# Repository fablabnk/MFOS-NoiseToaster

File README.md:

# MFOS Noise Toaster

> ##### Forked from *[Sam Zeter](https://github.com/samzeter/noise-toaster)*

## Status

Work in progress -> Revision 0.6.1

## Motivation

My first project to get back to electronics and learn something new along the way.
This repository is for the documentation of my journey to a fully functional analog synthesizer and may help other people to build one too.

This is my first electronics project for a long time and I decided to build the __Music From Outher Space -__ __*Noise Toaster*__,  because of the great documentation and the book 'Make: Analog Synthesizers' by Ray Wilson.

## How to use this repository

This repository contains all the files necessary for building the Noise Toaster, including the synth's PCB.  
If you intend to create your own PCB, simply compress all the files located in the 'PCB/Gerber Files' directory into a .zip file and upload it to the PCB manufacturer of your choice.   
In the directories 'classic design' and 'alternative design' (yet to come!) are all files to build the case of the Noise Toaster.    
For the front panels, I also created PCB designs, which you can upload to a manifacturer. Furthermore, there are CAD files and technical drawings (yet to come!) in the folders.   
The 'src' folder contains additional files which might be helpful.

## Project Structure
.  
│  
└── MFOS-NoiseToaster/  
&ensp;&ensp;&ensp;&ensp;│  
&ensp;&ensp;&ensp;&ensp;├── __'src/'__ &rarr; additional files and images that might be helpful for your own build   
&ensp;&ensp;&ensp;&ensp;├── __'classic design/'__ &rarr; all files to build the classic Noise Toaster case   
&ensp;&ensp;&ensp;&ensp;│&ensp;&ensp;&ensp;&ensp;├── __'CAD/'__  
&ensp;&ensp;&ensp;&ensp;│&ensp;&ensp;&ensp;&ensp;│&ensp;&ensp;&ensp;&ensp;└── '.FCstd' &rarr; FreeCAD files for the build    
&ensp;&ensp;&ensp;&ensp;│&ensp;&ensp;&ensp;&ensp;└── __'front panel/'__  
&ensp;&ensp;&ensp;&ensp;│&ensp;&ensp;&ensp;&ensp;&ensp;&ensp;&ensp;&ensp;&ensp;└── KiCAD files for front panel PCB &rarr; .zip this Geber files for the manufacturer   
&ensp;&ensp;&ensp;&ensp;├── __'PCB/'__   
&ensp;&ensp;&ensp;&ensp;│&ensp;&ensp;&ensp;&ensp;└── __'Gerber Files/'__ &rarr; .zip this directory for upload to the manufacturer  
&ensp;&ensp;&ensp;&ensp;│&ensp;&ensp;&ensp;&ensp;│&ensp;&ensp;&ensp;&ensp;└── *.gbr   
&ensp;&ensp;&ensp;&ensp;│&ensp;&ensp;&ensp;&ensp;└── 'Noise Toaster PCB.kicad_pcb'  
&ensp;&ensp;&ensp;&ensp;│&ensp;&ensp;&ensp;&ensp;└── ... &rarr; all files for the circuit diagram    
&ensp;&ensp;&ensp;&ensp;├── __'Bill of Material/'__   
&ensp;&ensp;&ensp;&ensp;│&ensp;&ensp;&ensp;&ensp;└── 'BoM checklist.md'  
&ensp;&ensp;&ensp;&ensp;│&ensp;&ensp;&ensp;&ensp;└── 'interactive BoM.html'    
&ensp;&ensp;&ensp;&ensp;├── README.md  
&ensp;&ensp;&ensp;&ensp;└── TODO.md  
&ensp;&ensp;&ensp;&ensp;└── licence.md &rarr; CC-BY-NC-SA  

## Usefull links and resources

* [Musik From Outer Space](http://musicfromouterspace.com/)
* [MFOS - Noise Toaster - Dokumentation](http://musicfromouterspace.com/index.php?MAINTAB=SYNTHDIY&PROJARG=NOISETOASTER/NOISETOASTER.php&VPW=1493&VPH=725)
* [Ray Wilson - YouTube Channel](https://www.youtube.com/@Musicfromouterspace)
* [MFOS Noise Toaster Presentation - Video by Ray Wilson](https://www.youtube.com/watch?v=smFKx6gfOd0)
* [Noise Toaster in action - Video by Ray Wilson](https://www.youtube.com/watch?v=qHlyuIe3wuU)
* [Make: Analog Synthesizers by Ray Wilson](https://learning.oreilly.com/library/view/make-analog-synthesizers/9781449356200/)

## For what's left TODO ...

[follow the White Rabbit!](TODO.md)

---

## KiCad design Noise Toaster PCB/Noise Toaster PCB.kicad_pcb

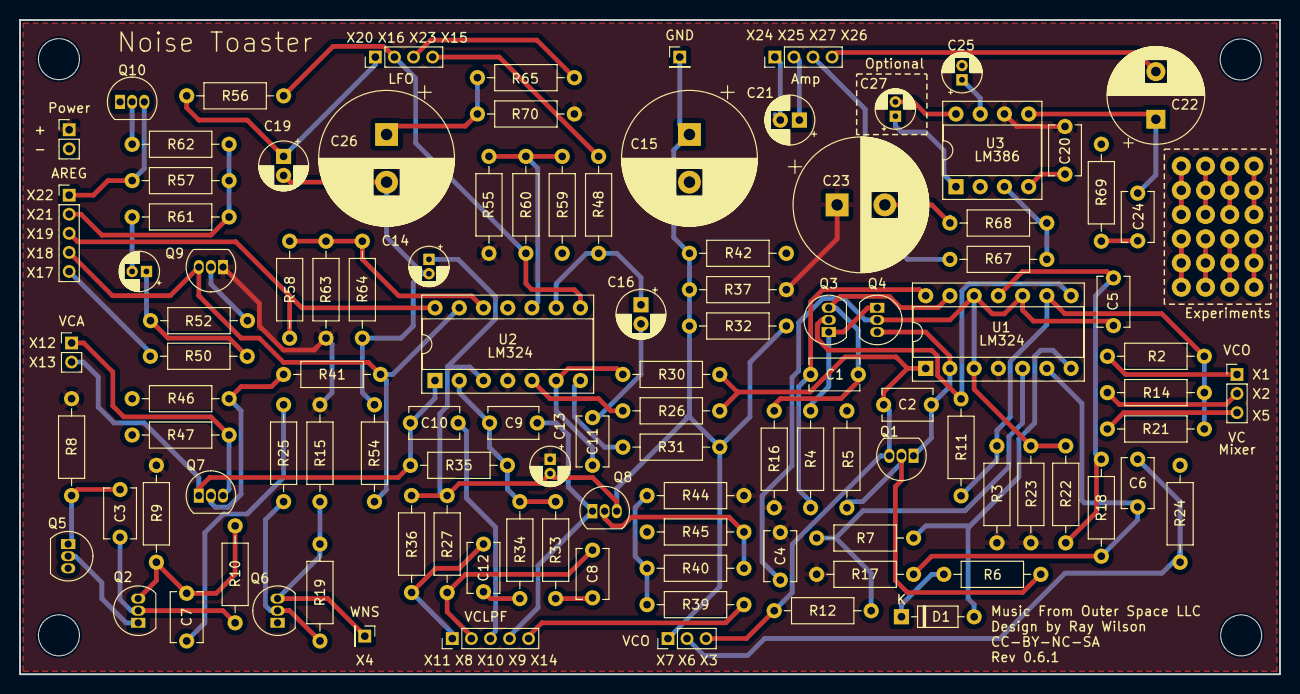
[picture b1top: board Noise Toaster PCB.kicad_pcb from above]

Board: 2 copper layers, 132.1 x 68.6 mm, 109 parts (0 on the bottom side), 68 nets.

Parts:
C1: 100 pF; C_Disc_D5.1mm_W3.2mm_P5.00mm
C2, C9, C10: 0.001 uF; C_Disc_D5.1mm_W3.2mm_P5.00mm
C3, C4, C5, C7, C8, C11, C12, C20: 0.1 uF; C_Disc_D5.1mm_W3.2mm_P5.00mm
C6: 0.01 uF; C_Disc_D5.1mm_W3.2mm_P5.00mm
C13, C14, C25, C27: 10 uF; CP_Radial_D4.0mm_P1.50mm
C15, C23, C26: 470 uF; CP_Radial_D14.0mm_P5.00mm
C16, C19, C21: 1 uF; CP_Radial_D5.0mm_P2.00mm
C18: 4.7 uF; CP_Radial_D4.0mm_P1.50mm
C22: 220 uF; CP_Radial_D10.0mm_P5.00mm
C24: 0.047 uF; C_Disc_D5.1mm_W3.2mm_P5.00mm
D1: D; D_DO-35_SOD27_P7.62mm_Horizontal
GND1: GND; PinHeader_1x01_P2.00mm_Vertical
J2: Power; PinHeader_1x02_P2.00mm_Vertical
J3: AREG; PinHeader_1x05_P2.00mm_Vertical
J4: LFO; PinHeader_1x04_P2.00mm_Vertical
J5, J6: VCO; PinHeader_1x03_P2.00mm_Vertical
J7: VCLPF; PinHeader_1x05_P2.00mm_Vertical
J8: VCA; PinHeader_1x02_P2.00mm_Vertical
J9: Amp; PinHeader_1x04_P2.00mm_Vertical
Q1, Q7, Q8, Q9: 2N5457; TO-92_Inline
Q2, Q3, Q4, Q5, Q6: 2N3904; TO-92_Inline
Q10: 2N3906; TO-92_Inline
R2: 75 K; R_Axial_DIN0207_L6.3mm_D2.5mm_P10.16mm_Horizontal
R3: 270 K; R_Axial_DIN0207_L6.3mm_D2.5mm_P10.16mm_Horizontal
R4, R6, R9, R12, R15, R17, R26, R32, R52, R61, R62: 10 K; R_Axial_DIN0207_L6.3mm_D2.5mm_P10.16mm_Horizontal
R5, R16, R30: 2 M; R_Axial_DIN0207_L6.3mm_D2.5mm_P10.16mm_Horizontal
R7: 300 K; R_Axial_DIN0207_L6.3mm_D2.5mm_P10.16mm_Horizontal
R8, R46: 1 M; R_Axial_DIN0207_L6.3mm_D2.5mm_P10.16mm_Horizontal
R10, R19, R41: 470 K; R_Axial_DIN0207_L6.3mm_D2.5mm_P10.16mm_Horizontal
R11: 2 K; R_Axial_DIN0207_L6.3mm_D2.5mm_P10.16mm_Horizontal
R14, R24, R25, R31, R44, R45, R47, R55, R58, R59, R60, R67: 100 K; R_Axial_DIN0207_L6.3mm_D2.5mm_P10.16mm_Horizontal
R18: 15 K; R_Axial_DIN0207_L6.3mm_D2.5mm_P10.16mm_Horizontal
R21: 36 K; R_Axial_DIN0207_L6.3mm_D2.5mm_P10.16mm_Horizontal
R22, R23: 4.7 K; R_Axial_DIN0207_L6.3mm_D2.5mm_P10.16mm_Horizontal
R27, R36: 47 K; R_Axial_DIN0207_L6.3mm_D2.5mm_P10.16mm_Horizontal
R33, R35: 4.7 M; R_Axial_DIN0207_L6.3mm_D2.5mm_P10.16mm_Horizontal
R34: 3 M; R_Axial_DIN0207_L6.3mm_D2.5mm_P10.16mm_Horizontal
R37, R42: 4.7 k; R_Axial_DIN0207_L6.3mm_D2.5mm_P10.16mm_Horizontal
R39, R40: 39 K; R_Axial_DIN0207_L6.3mm_D2.5mm_P10.16mm_Horizontal
R48, R65, R70: 3 K; R_Axial_DIN0207_L6.3mm_D2.5mm_P10.16mm_Horizontal
R50: 820 Ohm; R_Axial_DIN0207_L6.3mm_D2.5mm_P10.16mm_Horizontal
R54: 4,7 K; R_Axial_DIN0207_L6.3mm_D2.5mm_P10.16mm_Horizontal
R56, R68: 20 K; R_Axial_DIN0207_L6.3mm_D2.5mm_P10.16mm_Horizontal
R57: 200 Ohm; R_Axial_DIN0207_L6.3mm_D2.5mm_P10.16mm_Horizontal
R63, R64: 150 K; R_Axial_DIN0207_L6.3mm_D2.5mm_P10.16mm_Horizontal
R69: 10 Ohm; R_Axial_DIN0207_L6.3mm_D2.5mm_P10.16mm_Horizontal
U1, U2: LM324; DIP-14_W7.62mm_Socket
U3: LM386; DIP-8_W7.62mm_Socket
X4: WNS; PinHeader_1x01_P2.00mm_Vertical

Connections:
/AA: C2.1, Q1.1 (D), Q4.3 (C), U1.2 (-)
/ARG: J3.4, Q9.3 (S), R41.1, R54.2, U2.13 (-)
/Attack Release Envelope Generator/X17: J3.5, R50.2
/Attack Release Envelope Generator/X19: J3.3, R58.2, U2.14
/Attack Release Envelope Generator/X21: J3.2, R57.1, R61.2, R62.1
/Attack Release Envelope Generator/X22: J3.1, Q10.3 (C), R57.2
/Audio Amplifier/X24: C21.2, J9.1
/Audio Amplifier/X25: C21.1, J9.2
/Audio Amplifier/X26: C22.2, J9.4
/Audio Amplifier/X27: J9.3, R67.2
/FO: C10.2, J8.2, Q7.1 (D), R35.1, U2.1
/Front Panel/B: J4.2, R56.1, R60.2, U2.8
/Front Panel/X1: J5.1, R2.2
/Front Panel/X2: J5.2, R14.2
/Front Panel/X5: J5.3, R21.2
/Front Panel/X6: C6.1, J6.2, R24.1
/Front Panel/X8: C8.1, J7.2, R27.1
/Front Panel/X9: C9.1, J7.4, Q8.1 (D)
/Front Panel/X10: C10.1, J7.3
/Front Panel/X11: C12.1, J7.1, R36.2
/Front Panel/X12: J8.1, Q7.3 (S), R47.1
/Front Panel/X14: J7.5, R39.1
/Front Panel/X15: J4.4, R48.2
/Front Panel/X20: C19.1, J4.1, R56.2
/Front Panel/X23: J4.3, R65.2
/G2: C4.1, C5.1, Q4.2 (B), R22.1, R23.1, U1.3 (+), U1.10 (+), U1.12 (+)
/RMP: C2.2, J6.3, Q1.3 (S), R12.1, R26.1, R30.1, U1.1
/WNS: Q6.3 (C), R15.2, R19.1, X4.1
B+: C4.2, C13.1, C20.2, C23.1, J2.1, Q9.1 (D), R3.2, R8.1, R9.1, R15.1, R16.2, R17.2, R23.2, R37.1, R44.2, R55.1, R63.1, R70.2, U1.4 (V+), U2.4 (V+), U3.6 (V+)
B-: C5.2, C11.1, C14.2, C15.2, C16.2, C18.2, C19.2, C20.1, C23.2, C25.2, C26.2, J2.2, Q2.1 (E), Q5.2 (B), Q6.1 (E), Q10.1 (E), R5.2, R18.2, R22.2, R24.2, R42.2, R45.1, R46.2, R47.2, R54.1, R59.2, R61.1, R64.1, R68.2, R69.2, U1.11 (V-), U2.11 (V-), U3.2 (-), U3.4 (GND)
GND: C13.2, C14.1, C15.1, GND1.1, J6.1, Q8.3 (S), R27.2, R31.2, R32.1, R32.2, R36.1, R37.2, R42.1, U2.3 (+)
unnamed: C1.2, R4.2, U1.14
unnamed: C7.2, R25.1
unnamed: C8.2, R33.1
unnamed: C12.2, R34.1
unnamed: C18.1, R50.1, R52.1
unnamed: C22.1, C24.1, U3.5
unnamed: C24.2, R69.1
unnamed: C26.1, R65.1, R70.1
unnamed: C27.1, U3.1 (GAIN)
unnamed: C27.2, U3.8 (GAIN)
unnamed: D1.2 (A), R7.2, U1.7
unnamed: D1.1 (K), R6.2
unnamed: Q1.2 (G), R5.1, R6.1
unnamed: C3.2, Q2.2 (B), R10.2
unnamed: C7.1, Q2.3 (C), R9.2, R10.1
unnamed: Q3.2 (B), R11.2, U1.8
unnamed: C1.1, Q3.3 (C), R16.1, U1.13 (-)
unnamed: Q3.1 (E), Q4.1 (E), R4.1
unnamed: C3.1, Q5.1 (E), R8.2
unnamed: Q6.2 (B), R19.2, R25.2
unnamed: Q7.2 (G), R41.2, R46.1
unnamed: Q8.2 (G), R40.2, R45.2
unnamed: Q9.2 (G), R52.2
unnamed: Q10.2 (B), R62.2
unnamed: R31.1, U2.7
unnamed: R39.2, R40.1, R44.1
unnamed: R7.1, R12.2, U1.5 (+)
unnamed: C6.2, R17.1, R18.1, U1.6 (-)
unnamed: R2.1, R3.1, R11.1, R14.1, R21.1, U1.9 (-)
unnamed: C9.2, R33.2, R34.2, R35.2, U2.2 (-)
unnamed: R26.2, U2.5 (+)
unnamed: C11.2, R30.2, U2.6 (-)
unnamed: R55.2, R59.1, R60.1, U2.10 (+)
unnamed: C16.1, R48.1, U2.9 (-)
unnamed: R58.1, R63.2, R64.2, U2.12 (+)
unnamed: R67.1, R68.1, U3.3 (+)
unnamed: C25.1, U3.7 (BYPASS)

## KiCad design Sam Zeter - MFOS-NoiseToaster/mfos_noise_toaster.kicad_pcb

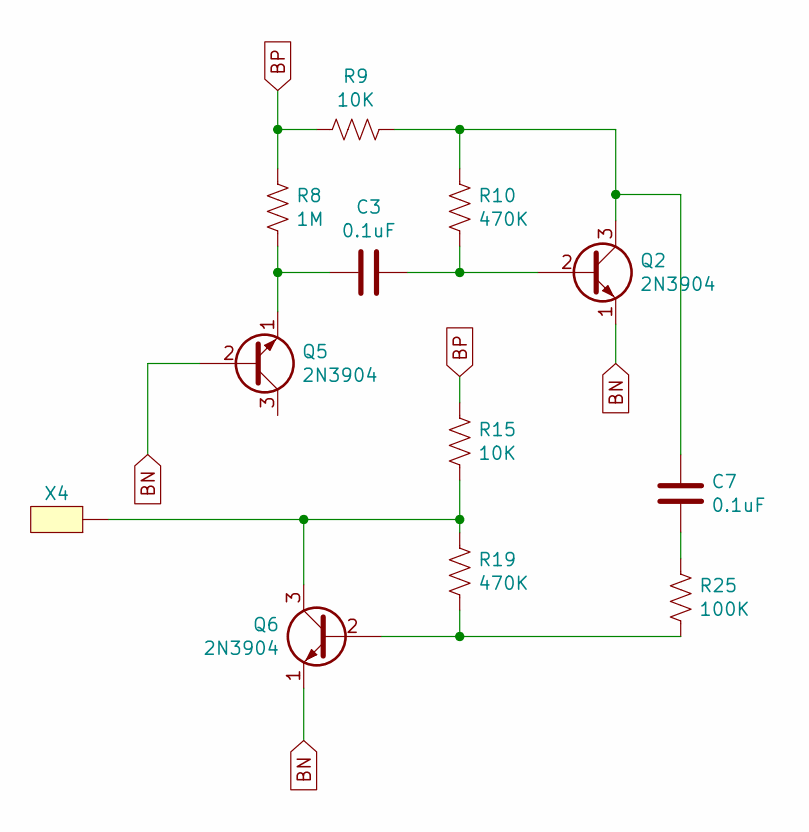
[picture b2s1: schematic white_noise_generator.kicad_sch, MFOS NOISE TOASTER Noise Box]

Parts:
C3, C7: 0.1uF; C_Disc_D5.0mm_W2.5mm_P3.50mm
Q2, Q5, Q6: 2N3904; TO-92_Inline
R8: 1M; R_Axial_DIN0207_L6.3mm_D2.5mm_P10.16mm_Horizontal
R9, R15: 10K; R_Axial_DIN0207_L6.3mm_D2.5mm_P10.16mm_Horizontal
R10, R19: 470K; R_Axial_DIN0207_L6.3mm_D2.5mm_P10.16mm_Horizontal
R25: 100K; R_Axial_DIN0207_L6.3mm_D2.5mm_P10.16mm_Horizontal
X4: Pad; pad

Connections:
BN: Q2.1 (E), Q5.2 (B), Q6.1 (E); also elsewhere on the board
BP: R8.1, R9.2, R15.1; also elsewhere on the board
unnamed: C3.1, Q2.2 (B), R10.2
unnamed: C3.2, Q5.1 (E), R8.2
unnamed: C7.1, R25.1
unnamed: C7.2, Q2.3 (C), R9.1, R10.1
unnamed: Q6.2 (B), R19.2, R25.2
unnamed: Q6.3 (C), R15.2, R19.1, X4.1

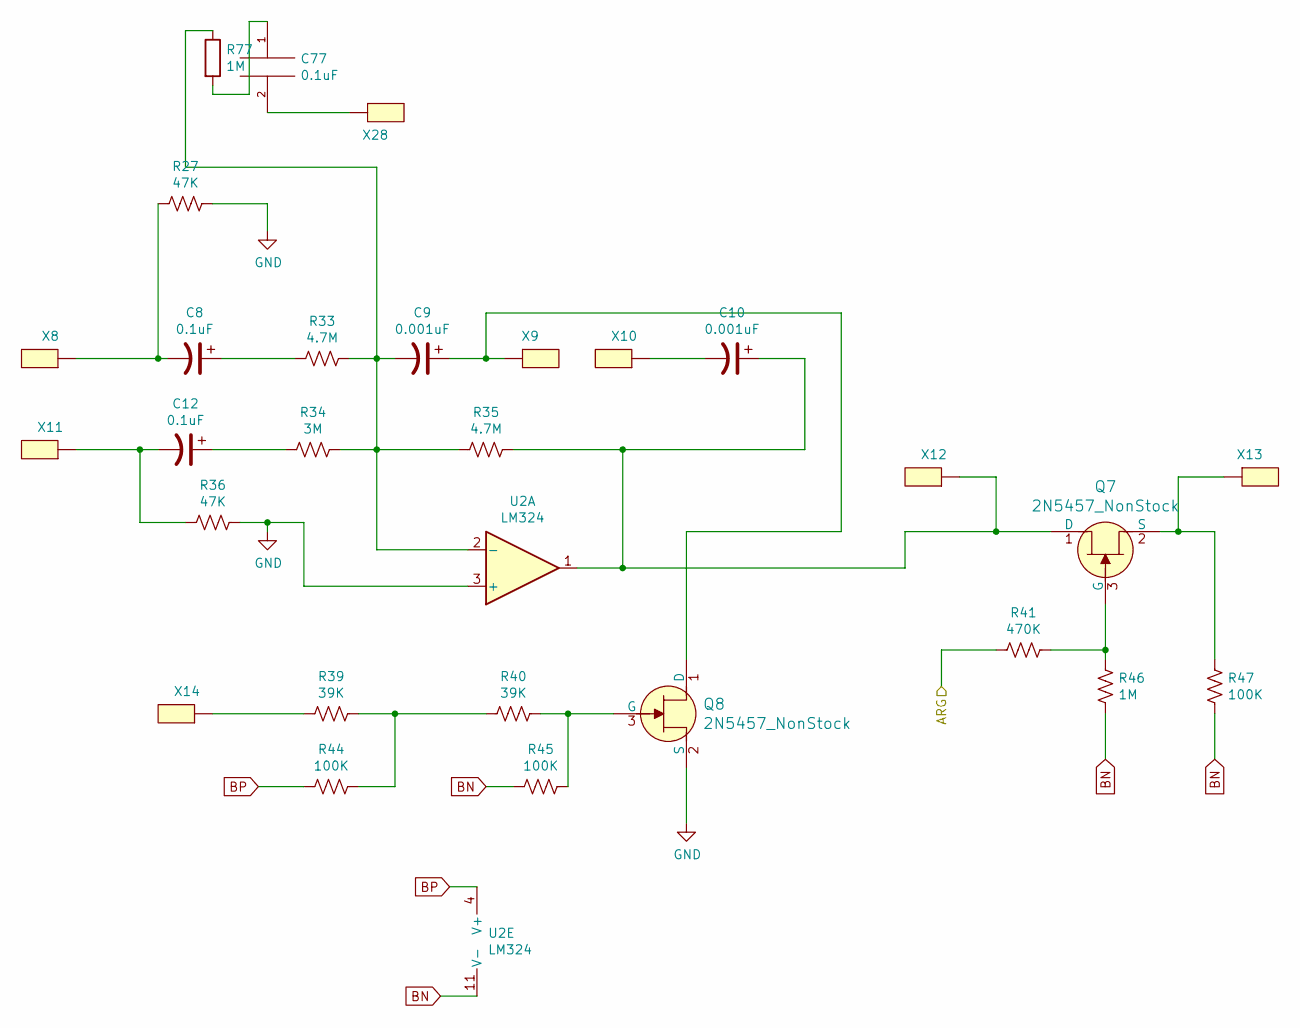
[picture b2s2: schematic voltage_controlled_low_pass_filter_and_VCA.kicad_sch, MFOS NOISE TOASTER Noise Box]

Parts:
C8, C12, C77: 0.1uF; C_Disc_D5.0mm_W2.5mm_P3.50mm
C9, C10: 0.001uF; C_Disc_D4.7mm_W2.5mm_P3.00mm
Q7, Q8: 2N5457_NonStock; TO-92-3; MPN 2N5457; Digi-Key_PN 2N5457-ND
R27, R36: 47K; R_Axial_DIN0207_L6.3mm_D2.5mm_P10.16mm_Horizontal
R33, R35: 4.7M; R_Axial_DIN0207_L6.3mm_D2.5mm_P10.16mm_Horizontal
R34: 3M; R_Axial_DIN0207_L6.3mm_D2.5mm_P10.16mm_Horizontal
R39, R40: 39K; R_Axial_DIN0207_L6.3mm_D2.5mm_P10.16mm_Horizontal
R41: 470K; R_Axial_DIN0207_L6.3mm_D2.5mm_P10.16mm_Horizontal
R44, R45, R47: 100K; R_Axial_DIN0207_L6.3mm_D2.5mm_P10.16mm_Horizontal
R46, R77: 1M; R_Axial_DIN0207_L6.3mm_D2.5mm_P10.16mm_Horizontal
U2: LM324; DIP-14_W7.62mm_LongPads
X8, X9, X10, X11, X12, X13, X14, X28: Pad; pad

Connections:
/attack_decay_generator/ARG: R41.1; also elsewhere on the board
BN: R45.2, R46.1, R47.1, U2.11 (V-); also elsewhere on the board
BP: R44.2, U2.4 (V+); also elsewhere on the board
GND: Q8.2 (S), R27.1, R36.1, U2.3 (+); also elsewhere on the board
unnamed: C8.1, R33.2
unnamed: C8.2, R27.2, X8.1
unnamed: C9.1, Q8.1 (D), X9.1
unnamed: C9.2, R33.1, R34.1, R35.2, R77.1, U2.2 (-)
unnamed: C10.1, Q7.1 (D), R35.1, U2.1, X12.1
unnamed: C10.2, X10.1
unnamed: C12.1, R34.2
unnamed: C12.2, R36.2, X11.1
unnamed: C77.1, R77.2
unnamed: C77.2, X28.1
unnamed: Q7.2 (S), R47.2, X13.1
unnamed: Q7.3 (G), R41.2, R46.2
unnamed: Q8.3 (G), R40.1, R45.1
unnamed: R39.1, R40.2, R44.1
unnamed: R39.2, X14.1

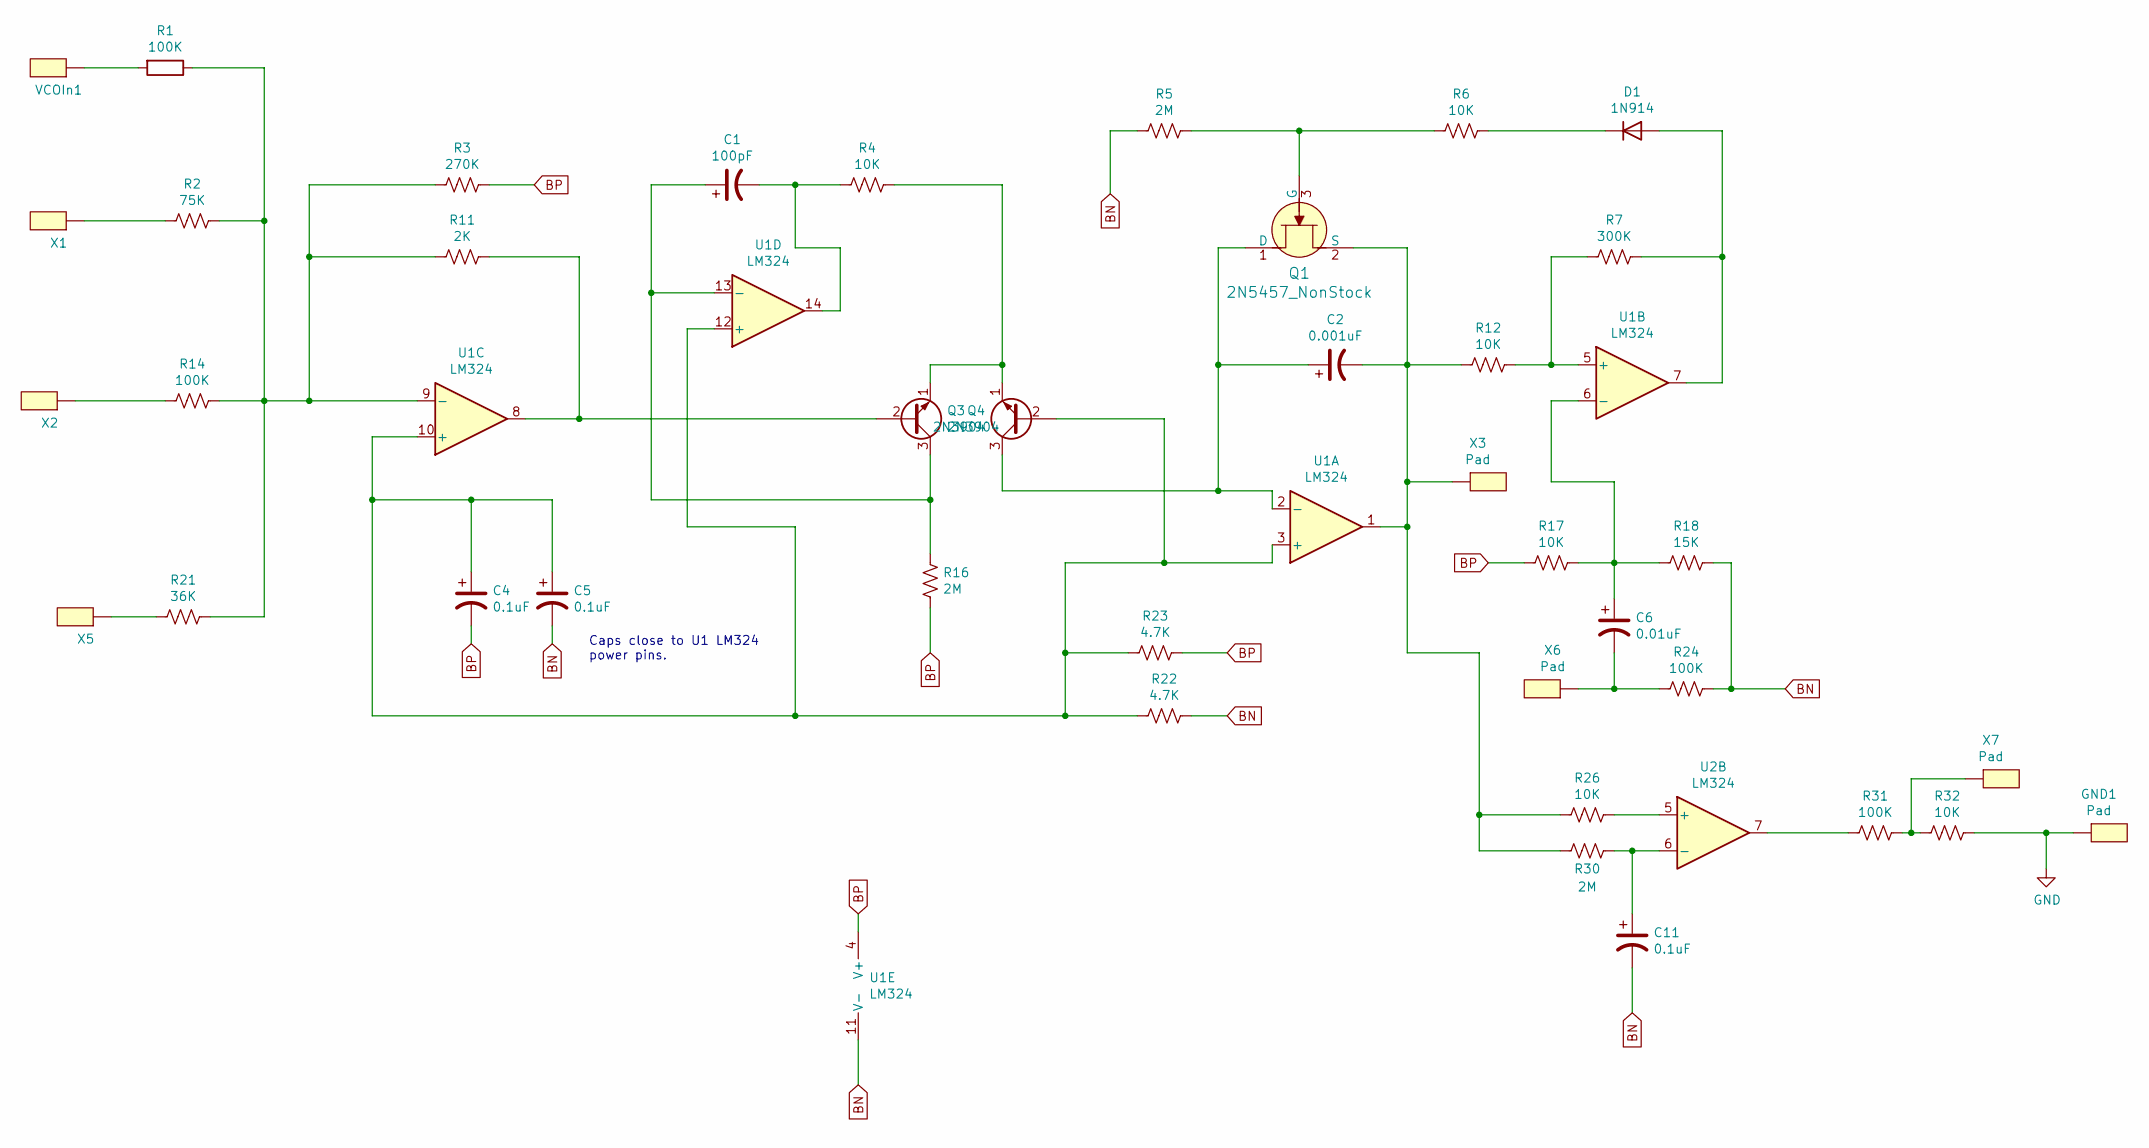
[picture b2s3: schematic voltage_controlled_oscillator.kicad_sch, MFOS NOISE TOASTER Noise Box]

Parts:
C1: 100pF; C_Disc_D3.4mm_W2.1mm_P2.50mm
C2: 0.001uF; C_Disc_D4.7mm_W2.5mm_P3.00mm
C4, C5, C11: 0.1uF; C_Disc_D5.0mm_W2.5mm_P3.50mm
C6: 0.01uF; C_Disc_D3.8mm_W2.6mm_P2.50mm
D1: 1N914; D_DO-35_SOD27_P7.62mm_Horizontal
GND1: Pad; pad
Q1: 2N5457_NonStock; TO-92-3; MPN 2N5457; Digi-Key_PN 2N5457-ND
Q3, Q4: 2N3904; TO-92_Inline
R1, R14, R24, R31: 100K; R_Axial_DIN0207_L6.3mm_D2.5mm_P10.16mm_Horizontal
R2: 75K; R_Axial_DIN0207_L6.3mm_D2.5mm_P10.16mm_Horizontal
R3: 270K; R_Axial_DIN0207_L6.3mm_D2.5mm_P10.16mm_Horizontal
R4, R6, R12, R17, R26, R32: 10K; R_Axial_DIN0207_L6.3mm_D2.5mm_P10.16mm_Horizontal
R5, R16, R30: 2M; R_Axial_DIN0207_L6.3mm_D2.5mm_P10.16mm_Horizontal
R7: 300K; R_Axial_DIN0207_L6.3mm_D2.5mm_P10.16mm_Horizontal
R11: 2K; R_Axial_DIN0207_L6.3mm_D2.5mm_P10.16mm_Horizontal
R18: 15K; R_Axial_DIN0207_L6.3mm_D2.5mm_P10.16mm_Horizontal
R21: 36K; R_Axial_DIN0207_L6.3mm_D2.5mm_P10.16mm_Horizontal
R22, R23: 4.7K; R_Axial_DIN0207_L6.3mm_D2.5mm_P10.16mm_Horizontal
U1, U2: LM324; DIP-14_W7.62mm_LongPads
VCOIn1: Pad; pad
X1, X2, X3, X5, X6, X7: Pad; pad

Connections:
BN: C5.2, C11.2, R5.2, R18.1, R22.1, R24.1, U1.11 (V-); also elsewhere on the board
BP: C4.2, R3.1, R16.2, R17.2, R23.1, U1.4 (V+); also elsewhere on the board
GND: GND1.1, R32.1; also elsewhere on the board
unnamed: C1.1, Q3.3 (C), R16.1, U1.13 (-)
unnamed: C1.2, R4.2, U1.14
unnamed: C2.1, Q1.1 (D), Q4.3 (C), U1.2 (-)
unnamed: C2.2, Q1.2 (S), R12.2, R26.2, R30.2, U1.1, X3.1
unnamed: C4.1, C5.1, Q4.2 (B), R22.2, R23.2, U1.3 (+), U1.10 (+), U1.12 (+)
unnamed: C6.1, R17.1, R18.2, U1.6 (-)
unnamed: C6.2, R24.2, X6.1
unnamed: C11.1, R30.1, U2.6 (-)
unnamed: D1.1 (K), R6.1
unnamed: D1.2 (A), R7.1, U1.7
unnamed: Q1.3 (G), R5.1, R6.2
unnamed: Q3.1 (E), Q4.1 (E), R4.1
unnamed: Q3.2 (B), R11.1, U1.8
unnamed: R1.1, R2.1, R3.2, R11.2, R14.1, R21.1, U1.9 (-)
unnamed: R1.2, VCOIn1.1
unnamed: R2.2, X1.1
unnamed: R7.2, R12.1, U1.5 (+)
unnamed: R14.2, X2.1
unnamed: R21.2, X5.1
unnamed: R26.1, U2.5 (+)
unnamed: R31.1, R32.2, X7.1
unnamed: R31.2, U2.7

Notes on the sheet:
Caps close to U1 LM324 power pins.

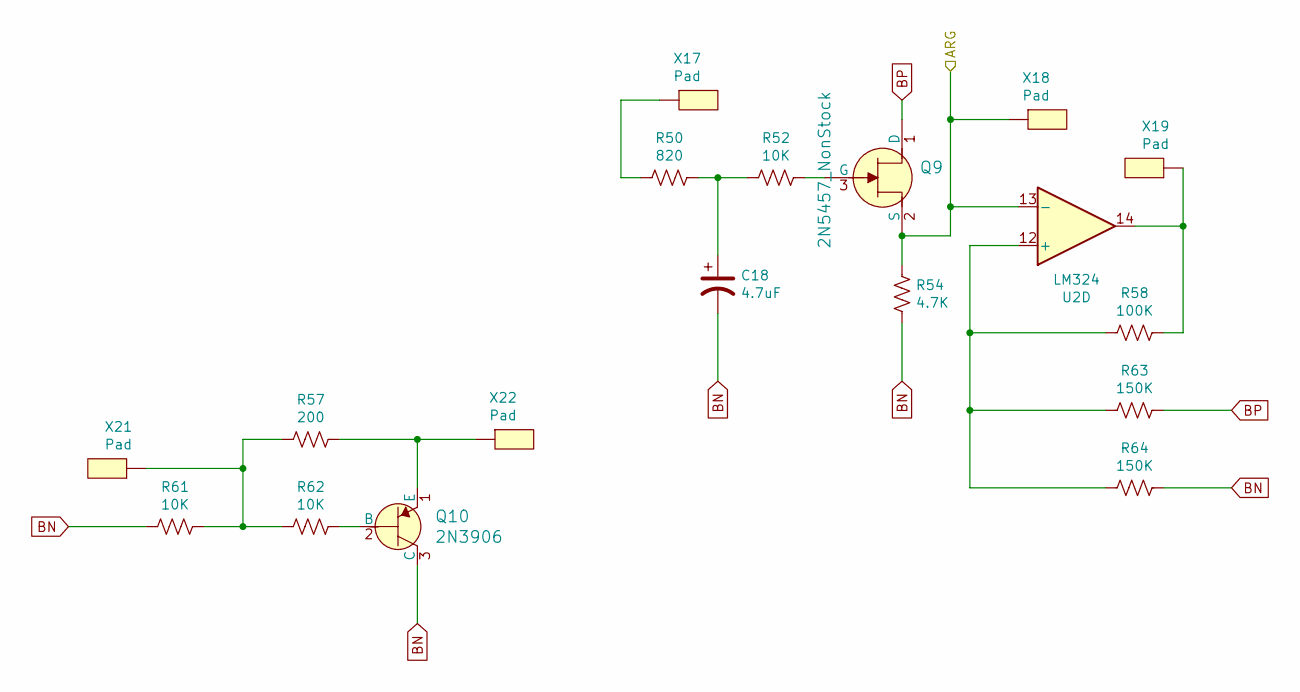
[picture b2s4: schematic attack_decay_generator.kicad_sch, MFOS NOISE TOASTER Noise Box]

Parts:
C18: 4.7uF; CP_Radial_D5.0mm_P2.50mm
Q9: 2N5457_NonStock; TO-92-3; MPN 2N5457; Digi-Key_PN 2N5457-ND
Q10: 2N3906; TO-92-3; MPN 2N3906; Digi-Key_PN 2N3906CS-ND
R50: 820; R_Axial_DIN0207_L6.3mm_D2.5mm_P10.16mm_Horizontal
R52, R61, R62: 10K; R_Axial_DIN0207_L6.3mm_D2.5mm_P10.16mm_Horizontal
R54: 4.7K; R_Axial_DIN0207_L6.3mm_D2.5mm_P10.16mm_Horizontal
R57: 200; R_Axial_DIN0207_L6.3mm_D2.5mm_P10.16mm_Horizontal
R58: 100K; R_Axial_DIN0207_L6.3mm_D2.5mm_P10.16mm_Horizontal
R63, R64: 150K; R_Axial_DIN0207_L6.3mm_D2.5mm_P10.16mm_Horizontal
U2: LM324; DIP-14_W7.62mm_LongPads
X17, X18, X19, X21, X22: Pad; pad

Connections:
/attack_decay_generator/ARG: Q9.2 (S), R54.2, U2.13 (-), X18.1; also elsewhere on the board
BN: C18.2, Q10.3 (C), R54.1, R61.2, R64.1; also elsewhere on the board
BP: Q9.1 (D), R63.1; also elsewhere on the board
unnamed: C18.1, R50.1, R52.2
unnamed: Q9.3 (G), R52.1
unnamed: Q10.1 (E), R57.1, X22.1
unnamed: Q10.2 (B), R62.1
unnamed: R50.2, X17.1
unnamed: R57.2, R61.1, R62.2, X21.1
unnamed: R58.1, U2.14, X19.1
unnamed: R58.2, R63.2, R64.2, U2.12 (+)

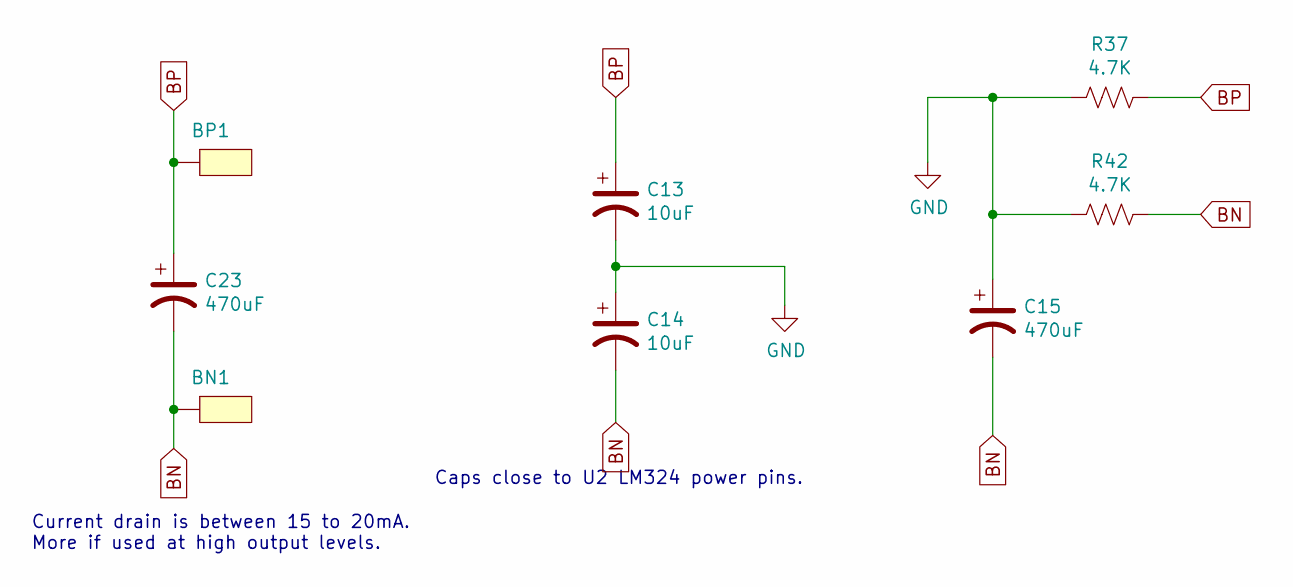
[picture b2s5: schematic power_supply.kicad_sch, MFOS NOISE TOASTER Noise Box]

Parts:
BN1: Pad-samz-symbol; pad
BP1: Pad-samz-symbol; pad
C13, C14: 10uF; CP_Radial_D5.0mm_P2.50mm
C15, C23: 470uF; CP_Radial_D10.0mm_P5.50mm
R37, R42: 4.7K; R_Axial_DIN0207_L6.3mm_D2.5mm_P10.16mm_Horizontal

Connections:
BN: BN1.1, C14.2, C15.2, C23.2, R42.1; also elsewhere on the board
BP: BP1.1, C13.1, C23.1, R37.1; also elsewhere on the board
GND: C13.2, C14.1, C15.1, R37.2, R42.2; also elsewhere on the board

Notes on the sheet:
Caps close to U2 LM324 power pins.
Current drain is between 15 to 20mA. More if used at high output levels.

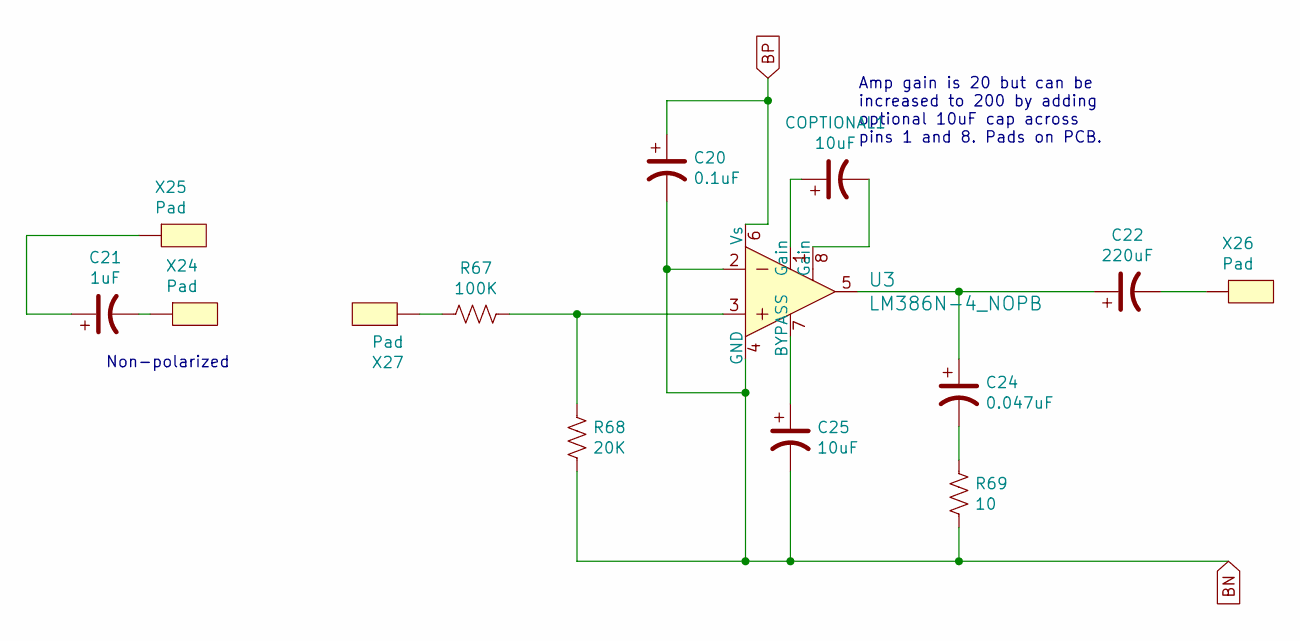
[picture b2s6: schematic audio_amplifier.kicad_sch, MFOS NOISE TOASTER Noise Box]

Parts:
C20: 0.1uF; C_Disc_D5.0mm_W2.5mm_P3.50mm
C21: 1uF; CP_Radial_D5.0mm_P2.50mm
C22: 220uF; CP_Radial_D10.0mm_P5.00mm
C24: 0.047uF; C_Disc_D3.4mm_W2.1mm_P2.50mm
C25: 10uF; CP_Radial_D5.0mm_P2.50mm
COPTIONAL1: 10uF; CP_Radial_D5.0mm_P2.50mm
R67: 100K; R_Axial_DIN0207_L6.3mm_D2.5mm_P10.16mm_Horizontal
R68: 20K; R_Axial_DIN0207_L6.3mm_D2.5mm_P10.16mm_Horizontal
R69: 10; R_Axial_DIN0207_L6.3mm_D2.5mm_P10.16mm_Horizontal
U3: LM386N-4_NOPB; DIP-8_W7.62mm; MPN LM386N-4/NOPB; Digi-Key_PN 296-43960-5-ND
X24, X25, X26, X27: Pad; pad

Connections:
BN: C20.2, C25.2, R68.2, R69.2, U3.2, U3.4 (GND); also elsewhere on the board
BP: C20.1, U3.6 (Vs); also elsewhere on the board
unnamed: C21.1, X25.1
unnamed: C21.2, X24.1
unnamed: C22.1, C24.1, U3.5
unnamed: C22.2, X26.1
unnamed: C24.2, R69.1
unnamed: C25.1, U3.7 (BYPASS)
unnamed 36: COPTIONAL1.1, U3.1 (Gain); also elsewhere on the board
unnamed 37: COPTIONAL1.2, U3.8 (Gain); also elsewhere on the board
unnamed: R67.1, R68.1, U3.3
unnamed: R67.2, X27.1

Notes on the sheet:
Non-polarized
Amp gain is 20 but can be increased to 200 by adding optional 10uF cap across pins 1 and 8. Pads on PCB.

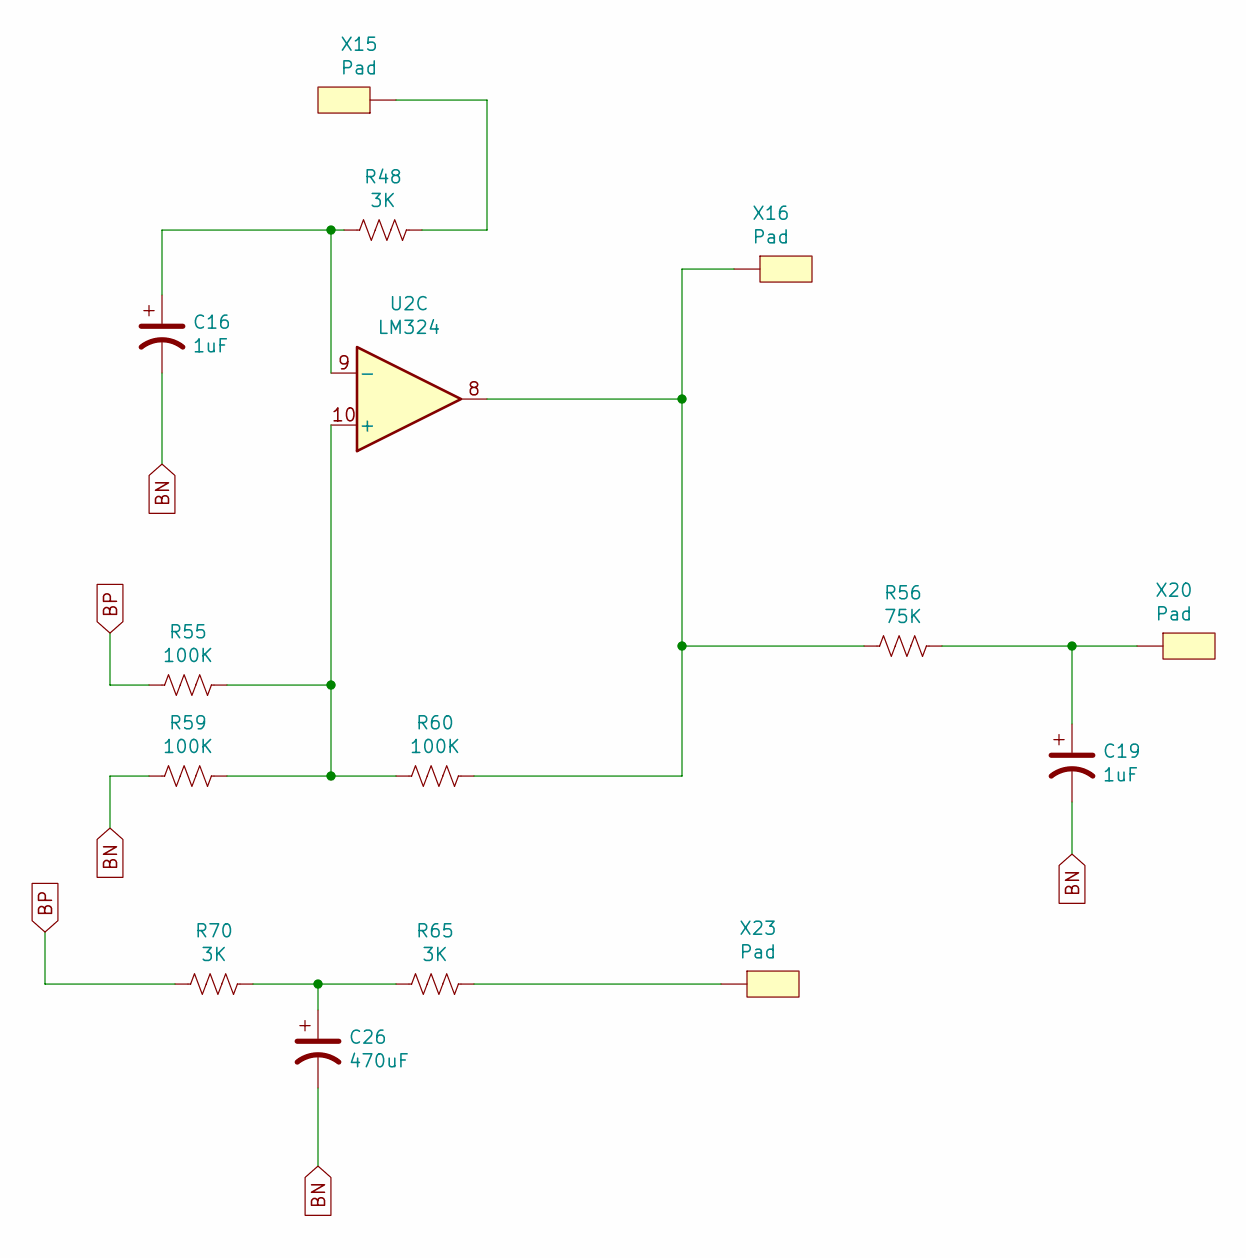
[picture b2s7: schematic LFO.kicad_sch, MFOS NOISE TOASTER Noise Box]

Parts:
C16, C19: 1uF; CP_Radial_D5.0mm_P2.50mm
C26: 470uF; CP_Radial_D10.0mm_P5.00mm
R48, R65, R70: 3K; R_Axial_DIN0207_L6.3mm_D2.5mm_P10.16mm_Horizontal
R55, R59, R60: 100K; R_Axial_DIN0207_L6.3mm_D2.5mm_P10.16mm_Horizontal
R56: 75K; R_Axial_DIN0207_L6.3mm_D2.5mm_P10.16mm_Horizontal
U2: LM324; DIP-14_W7.62mm_LongPads
X15, X16, X20, X23: Pad; pad

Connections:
BN: C16.2, C19.2, C26.2, R59.2; also elsewhere on the board
BP: R55.2, R70.2; also elsewhere on the board
unnamed: C16.1, R48.2, U2.9 (-)
unnamed: C19.1, R56.1, X20.1
unnamed: C26.1, R65.2, R70.1
unnamed: R48.1, X15.1
unnamed: R55.1, R59.1, R60.2, U2.10 (+)
unnamed: R56.2, R60.1, U2.8, X16.1
unnamed: R65.1, X23.1

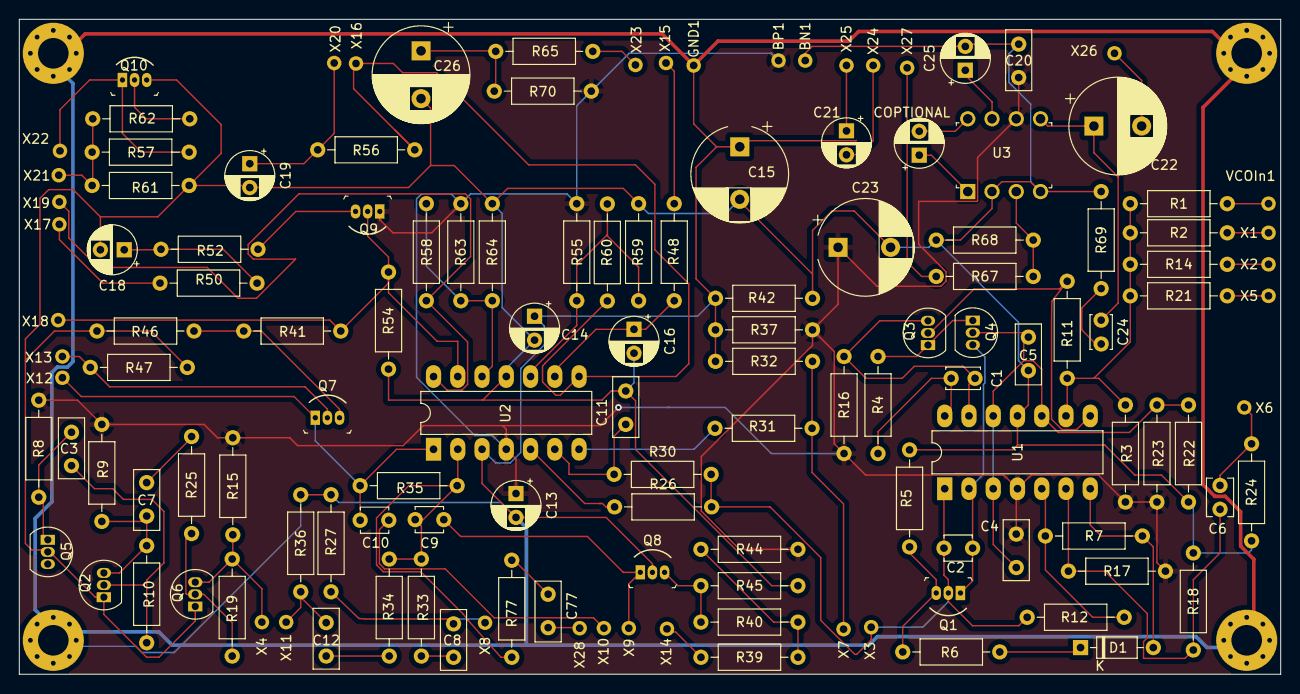
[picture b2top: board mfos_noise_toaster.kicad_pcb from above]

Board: 2 copper layers, 132.1 x 68.6 mm, 134 parts (0 on the bottom side), 72 nets.

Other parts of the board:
COPTIONAL: 10uF; CP_Radial_D5.0mm_P2.50mm

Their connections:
unnamed 36: COPTIONAL.1; also elsewhere on the board
unnamed 37: COPTIONAL.2; also elsewhere on the board

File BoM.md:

# Bill of Materials for MFOS Noise Toaster


### Active Components
|   Check  |    Qty   | Description | Value/Note | Designators |
|:--------:|:--------:|:-----------:|:----------:|:-----------:|
| &#9744;  | 2 | LM324 Quad Low Power Op Amp | 14 pin DIP | U1, U2 |
| &#9744;  | 1 | LM386N4 (or N3) Low Voltage Audio Power Amp | 8 pin DIP | U3 |
| &#9744;  | 1 | 2N3906 PNP Transistor | T092 | Q10 |
| &#9744;  | 4 | 2N5457 N Channel JFET | T092 | Q1, Q7, Q8, Q9 |
| &#9744;  | 5 | 2N3904 NPN Transistor | T092 | Q2, Q3, Q4, Q5, Q6 |
| &#9744;  | 3 | 1N914 High Speed Sw. Diode | D0-35 | D1, D2, D3 |
| &#9744;  | 1 | LED | General Purpose | LED1 |
| &#9744;  | 2 | 14 pin DIP IC Socket | High Reliability |  |
| &#9744;  | 1 | 8 pin DIP IC Socket | High Reliability |  |

### Resistors and Pots
|   Check  |    Qty   | Description | Value/Note | Designators |
|:--------:|:--------:|:-----------:|:----------:|:-----------:|
| &#9744;  | 7 | Linear Taper Potentiometer | 100 k&ohm; | R1, R13, R20, R28, R29, R38, R66 |
| &#9744;  | 3 | Linear Taper Potentiometer | 1 M&ohm; | R49, R51, R53 |
| &#9744;  | 3 | Resistor 0,25 W 5 % | 2 M&ohm; | R5, R16, R53 |
| &#9744;  | 1 | Resistor 0,25 W 5 % | 300 k&ohm; | R7 |
| &#9744;  | 1 | Resistor 0,25 W 5 % | 36 k&ohm; | R21 |
| &#9744;  | 1 | Resistor 0,25 W 5 % | 15 k&ohm; | R18 |
| &#9744;  | 2 | Resistor 0,25 W 5 % | 39 k&ohm; | R39, R40 |
| &#9744;  | 3 | Resistor 0,25 W 5 % | 3 k&ohm; | R48, R65, R70 |
| &#9744;  | 5 | Resistor 0,25 W 5 % | 4.7 k&ohm; | R22, R23, R37, R42, R54 |
| &#9744;  | 2 | Resistor 0,25 W 5 % | 4.7 M&ohm; | R33, R35 |
| &#9744;  | 3 | Resistor 0,25 W 5 % | 470 k&ohm; | R10, R19, R41 |
| &#9744;  | 2 | Resistor 0,25 W 5 % | 47 k&ohm; | R27, R36 |
| &#9744;  | 1 | Resistor 0,25 W 5 % | 75 k&ohm; | R2 |
| &#9744;  | 1 | Resistor 0,25 W 5 % | 820 &ohm; | R50 |
| &#9744;  | 1 | Resistor 0,25 W 5 % | 10 &ohm; | R69 |
| &#9744;  | 12 | Resistor 0,25 W 5 % | 100 k&ohm; | R14, R24, R25, R31, R44, R45, R47, R55, R58, R59, R60, R67 |
| &#9744;  | 11 | Resistor 0,25 W 5 % | 10 k&ohm; | R4, R6, R9, R12, R15, R17, R26, R32, R52, R61, R62  |
| &#9744;  | 2 | Resistor 0,25 W 5 % | 150 &ohm; | R63, R64 |
| &#9744;  | 1 | Resistor 0,25 W 5 % | 3 M&ohm; | R34 |
| &#9744;  | 2 | Resistor 0,25 W 5 % | 1 M&ohm; | R8, R46 |
| &#9744;  | 1 | Resistor 0,25 W 5 % | 200 &ohm; | R57 |
| &#9744;  | 2 | Resistor 0,25 W 5 % | 20 k&ohm; | R68, R56 |
| &#9744;  | 1 | Resistor 0,25 W 5 % | 270 k&ohm; | R3 |
| &#9744;  | 1 | Resistor 0,25 W 5 % | 27 k&ohm; | R43 |
| &#9744;  | 1 | Resistor 0,25 W 5 % | 2 k&ohm; | R11 |

### Capacitors
|   Check  |    Qty   | Description | Value/Note | Designators |
|:--------:|:--------:|:-----------:|:----------:|:-----------:|
| &#9744;  | 2 | Capacitor Aluminum Bipolar (nonpolarized) | 1 &micro;F | C17, C21 |
| &#9744;  | 3 | Capacitor Ceramic | 0.001 &micro;F / 1 nF | C2, C9, C10 |
| &#9744;  | 1 | Capacitor Ceramic | 0.047 &micro;F / 47 nF | C24 |
| &#9744;  | 8 | Capacitor Ceramic | 0.1 &micro;F / 100 nF | C3, C4, C5, C7, C8, C11, C12, C20 |
| &#9744;  | 1 | Capacitor Ceramic | 100 pF | C1 |
| &#9744;  | 1 | Capacitor Ceramic | 0.01 &micro;F / 10 nF | C6 |
| &#9744;  | 3 | Capacitor Electrolytic | 10 &micro;F | C13, C14, C25 |
| &#9744;  | 2 | Capacitor Electrolytic | 1 &micro;F | C16, C19 |
| &#9744;  | 1 | Capacitor Electrolytic | 4.7 &micro;F | C18 |
| &#9744;  | 1 | Capacitor Electrolytic Radial Lead 0.2" Spacing | 220 &micro;F | C22 |
| &#9744;  | 3 | Capacitor Electrolytic Radial Lead 0.2" Spacing | 470 &micro;F | C15, C23, C26 |

### Hardware and Other Components
|   Check  |    Qty   | Description | Value/Note | Designators |
|:--------:|:--------:|:-----------:|:----------:|:-----------:|
| &#9744;  | 1 | Speaker 2 1/4" | 8 &ohm; 1 W | SPK1 |
| &#9744;  | 2 | Switch SPDT (Center Off) Mini Toggle | SPDT C.O. | S3, S6 |
| &#9744;  | 2 | Switch SPDT Mini Toggle | SPDT | S8, S9 |
| &#9744;  | 6 | Switch SPST Mini Toggle | SPST | S1, S2, S4, S5, S7, S11 |
| &#9744;  | 1 | Switch SPST N.O. Pushbutton | SPST | S10 |
| &#9744;  | 1 | Jack 1/4" with NC Switch to Tip |  | J1 |
| &#9744;  | 1 | 9V Alkaline Battery |  | B1 |
| &#9744;  | 1 | 9V Battery Snap Connector |  |  |
| &#9744;  | 1 | 9V Battery Holder |  |  |
| &#9744;  | 1 | Projec Case 7 * 7 * 2" |  |  |
| &#9744;  | 2 | 6-32 1 1/4" Screws |  |  |
| &#9744;  | 4 | 6-32 Screw Nuts |  |  |
| &#9744;  | 4 | 1/4" W x 3/8" L Nylon Spacers |  | 1 |

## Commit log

2023-07-12 added own README as test
2023-07-12 added README.md
2023-07-12 added .gitignore
2023-07-12 refactored the gerber files
2023-07-12 fixed typo because me at english bad o_O
2023-07-17 added Bills of Materials as .md file
2023-07-17 fixed check box
2023-07-30 added the classic noise toaster front panel design
2023-07-30 updated rotary scales of the front panel design
2023-07-30 added invertet front panel version
2023-08-07 updated .gitignore with KiCad files
2023-08-07 added a proper license for the files
2023-08-07 fixed typo
2023-08-21 updated TODO
2023-08-21 updated .gitignore file
2023-08-21 commiting my KiCad schematics
2023-08-21 updated .gitignore
2023-08-21 outsourced TODO and added project structure
2023-08-21 updated project structure and front panel dir
2023-08-21 added seperated TODO.md file
2023-08-21 updated tree view
2023-08-21 fixed tree view
2023-08-23 beatified the tree view
2023-08-24 updated schematics
2023-08-26 erstelle test.txt
2023-08-26 cloned sam zeters original repository
2023-08-26 deleted unnecessary files
2023-08-26 try to resole '2 commits behind messsage'
2023-08-26 solved issues
2023-08-26 fixed final gerber location
2023-08-26 refactored the schematic
2023-09-10 refactored schematics and added front panel
2023-09-10 beautified README and fixed typo
2023-09-10 added lost .gitignore
2023-09-10 cleared gitignore cache
2023-09-10 fixed typo in gitignore
2023-09-10 fixed another typo
2023-09-10 removed old pcb files
2023-09-10 color coded wireing and added color legend
2023-09-10 front panel components excluded from circuit board
2023-09-10 fixed legend
2023-09-10 wireing and components have been checked
2023-09-12 applied footprints
2023-09-17 placed pards of the pcb properly
2023-09-18 created pcb file
2023-09-18 created gerber files
2023-09-18 created interactive BoM
2023-09-18 added .zip files to .gitignore
2023-09-18 updated project structure section
2023-09-18 updated tree few in README.md
2023-09-27 rerooted some circuit paths
2023-09-27 updated BoM
2023-09-27 updated gerber files
2023-10-11 changed the pcb to the original size factor
2023-10-12 beautified pcb
2023-10-27 changed header pins to groups
2023-10-27 updated interactive Bill of Material
2023-10-28 fixed silkscreen layer
2023-10-29 fixed minor issues with the pcb
2023-10-29 updated BoM and README.md
2024-01-05 updated .gitignore for FreeCAD
2024-01-05 commit FreeCAD classic Noise Toaster Files
2024-01-06 finished the classic case design
2024-01-07 updated case
2024-03-13 added front panel pcb
2024-03-21 deleted .idea folder, what the heck o_O
2024-03-24 finished classic front panel
2024-03-24 refactored the project
2024-03-25 updated license text
2025-02-21 minor revisions to PCB to avoid isolated islands

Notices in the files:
Noise Toaster PCB/Noise Toaster PCB.kicad_pcb:
Licence: CC-BY-NC-SA
